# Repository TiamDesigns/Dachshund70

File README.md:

# Dachshund70

A tri-mode 60% keyboard I'm designing from scratch: the PCBs, the switch plate, the firmware, the config protocol, the driver and the configurator app. It runs over USB, Bluetooth LE and its own 2.4 GHz dongle, all on the nRF52840.

It was called the Dachshund60F until November 2026; older notes, PRs and the 26 October project review still use that name.

No boards have been made yet. All three PCBs are designed and the firmware is built and tested on a PC, so the next step is ordering them and bringing them up.

## Why I'm building this

I'm using this project to do two things at once:

1. **Explore hardware design with AI.** I want to see how far I can push an AI-assisted workflow on a real product: schematics, PCB layout, firmware, tooling and docs. I make the decisions and review everything, and Claude Code does a lot of the legwork. This repo is the record of how that went.
2. **Learn high-speed peripherals properly.** A keyboard looks simple, but doing it right covers USB device design, Bluetooth LE, a proprietary 2.4 GHz radio link, SPI and I2C displays, addressable LEDs, flash storage and power management. I want to understand each one well enough to design it, not just copy it.

And at the end of it I want a keyboard I actually enjoy using every day.

## Project goals

### Hardware

- Design all the boards myself in KiCad: the mainboard, a USB-C daughterboard and the dongle, plus an FR4 switch plate.
- Use a pre-certified nRF52840 module (Raytac MDBT50Q-P1MV2) and get the antenna keep-out, power and USB right the first time.
- Make it nice to type on: hot-swap switches, screw-in stabilisers, a gasket-mounted plate, and a horizontal roller encoder that turns like a mouse wheel.
- Run from USB or a single LiPo cell, with proper charging and a power path so it still works with the battery switched off.
- Measure everything when the boards arrive: rails, current draw in every state, scan rate, latency and radio range. The plan is in [docs/bringup-test-plan.md](docs/bringup-test-plan.md).

### Firmware

- Write my own firmware on Zephyr / nRF Connect SDK, not a fork of QMK or ZMK.
- Keep the keymap logic in plain C with no hardware in it, so it runs as unit tests on a PC.
- Be a complete USB keyboard: NKRO with boot-protocol fallback for BIOS and KVMs, media keys, lock LEDs, and suspend and remote wakeup.
- Support the advanced stuff: tap-hold, combos, tap dance, macros, key overrides, Caps Word, Auto Shift, Leader, mouse keys and the encoder.
- Never crash or corrupt flash on a bad packet. Every index and length from the host is checked, and the parser is fuzzed.

### Wireless

- Bluetooth LE HID with several host profiles and a switch key.
- A 2.4 GHz dongle on a second nRF52840 with low latency, polling at 1000 Hz (the limit for full-speed USB).
- Battery reporting, idle sleep and wake on key press.

### Driver and app

- No kernel driver. The board shows up as a normal HID keyboard plus one vendor-defined HID interface for configuration, so it works anywhere with nothing to install.
- A TypeScript host library (the "driver") that talks to that interface over WebHID in the browser or node-hid on the desktop.
- **Doghouse**, the configurator: keymap editing, advanced keys, macros, settings and firmware updates. It runs in Chrome or Edge, or as a desktop app for Windows, macOS and Linux that updates itself. It's in warm earth tones and dog-themed, because the boards are named after dogs.

### Doing it properly

- One protocol definition (`protocol/protocol.yaml`), with the C and TypeScript code generated from it.
- Versioned, CRC-checked, wear-levelled settings in flash, with migrations.
- CI that runs the unit tests, the host-library tests, the app build, protocol fuzzing, and debug and release firmware builds on every PR.
- Write down what changed and what's been tested in [PROGRESS.md](PROGRESS.md).

## The board

| | |
| --- | --- |
| MCU | nRF52840 (Raytac MDBT50Q-P1MV2 module) |
| Layout | 60% with an F-row, 80 switch positions, split or 6.25u spacebar |
| Matrix | 6 × 15, COL2ROW, diodes on every switch |
| Switches | Kailh hot-swap sockets (3 soldered positions on the spacebar row) |
| Encoder | Bourns PEC12R-2230F-S0024: shaft parallel to the board, 24 detents, push switch, 30 mm shaft, used as a 2u roller. On its own module board, cabled to the mainboard |
| Lighting | 6 × SK6812MINI-E indicators: layer, a 4-step battery gauge, and Caps Lock. No per-key RGB |
| Display | Optional OLED or e-paper on header J4 (panel not chosen yet) |
| Power | USB-C on a daughterboard, 1S LiPo on JST-PH, MCP73831 charger with a load-sharing power path |
| Connectivity | USB, Bluetooth LE, 2.4 GHz dongle |
| Bootloader | Adafruit nRF52 UF2 bootloader: double-tap reset and drag a `.uf2` onto the drive |
| USB IDs | pid.codes test PIDs 1209:0001 (keyboard), 1209:0002 (dongle), 1209:0003 (bootloader) |

## Where it's at

The firmware follows the build order in [SPEC.md](SPEC.md): wired first, then wireless.

| Phase | What it covers | Status |
| --- | --- | --- |
| 1 | Scaffold: monorepo, CI, Zephyr app | Done |
| 2 | Board bring-up, USB enumeration, UF2 bootloader | Done |
| 3 | Matrix scan, debounce, keycodes, layers, tap-hold | Done |
| 4 | Full USB HID: NKRO, media keys, lock LEDs, sleep and wake | Done |
| 5 | Config protocol v1 over a vendor HID interface | Done |
| 6 | Saving settings to flash | Done |
| 7 | Host library (WebHID and node-hid) | Done |
| 8 | Doghouse on real boards | Done |
| 9 | Advanced keys, macros and the encoder | Done |
| 10 | Indicator colours and global settings | Done |
| 11 | In-app firmware updates | Done |
| 12 | Bluetooth LE | Done |
| 13 | Power management, battery and input delay | Done |
| 14 | 2.4 GHz dongle firmware | Done |
| 15 | Desktop app packaging and auto-update | Done |

"Done" means built and tested on a PC and in CI. None of it has run on a real board yet, because there isn't one.

## Repo layout

| Folder | What's in it |
| --- | --- |
| `hardware/` | KiCad 10 projects: mainboard, USB-C daughterboard, dongle and plate, STEP exports, and the case (`hardware/case/`, CadQuery) |
| `boards/Dachshund70/` | Pin map, keyboard definition, Zephyr board files and the UF2 bootloader board |
| `boards/Pup/` | A one-key test board: the keyboard firmware on Nordic's nRF52840 Dongle, for trying the wireless outputs before the PCB exists |
| `firmware/` | The keyboard firmware. `firmware/core/` is the hardware-free keymap engine and its tests |
| `dongle/` | 2.4 GHz receiver firmware (see `dongle/README.md` to flash and pair it) |
| `protocol/` | `protocol.yaml` and the code generator |
| `host-lib/` | The TypeScript host library, mock board and tests |
| `app/` | Doghouse, the configurator (Svelte 5 + Vite), and its desktop app in `app/src-tauri/` (Tauri) |
| `docs/` | Bring-up and test plan, and my design decisions |

## Trying it out

You don't need a board to play with most of it.

**Doghouse with demo boards**

```sh
cd app
npm install
npm run dev
```

Then open http://localhost:5173/?demo. To use a real board, open http://localhost:5173 in Chrome or Edge and click **Connect a board…**.

**Tests**

```sh
# keymap engine and protocol (C, runs on the PC)
cmake -S firmware/core -B firmware/core/build
cmake --build firmware/core/build
ctest --test-dir firmware/core/build --output-on-failure

# host library
cd host-lib && npm ci && npm test
```

**Firmware**

From an nRF Connect SDK v3.4.1 shell, in the repo root:

```sh
west build -p -b dachshund70/nrf52840 -d build/firmware firmware -- -DBOARD_ROOT="$PWD"
```

[CLAUDE.md](CLAUDE.md) has every command, including release builds, display panels, the bootloader and flashing.

## Docs

- [SPEC.md](SPEC.md): scope and build order
- [PROGRESS.md](PROGRESS.md): what's done, what's tested, known issues
- [docs/design-decisions.md](docs/design-decisions.md): the decisions I made along the way and what I've learnt
- [docs/bringup-test-plan.md](docs/bringup-test-plan.md): how each board gets flashed, tested and measured
- [protocol/README.md](protocol/README.md): the config protocol
- [SCHEDULED_TASKS.md](SCHEDULED_TASKS.md): open tasks

## Licence and disclaimer

This is open source and open hardware. You're free to copy it, change it, build it and sell it.

- **Code** (firmware, host library, Doghouse, protocol, scripts) is under the [MIT License](LICENSE).
- **Hardware** (everything in `hardware/`: the three PCBs and the plate) is under the [CERN Open Hardware Licence v2, Permissive](hardware/LICENSE) (CERN-OHL-P-2.0).
- **Third-party files** keep their own licences. The keyswitch footprints and 3D models are CC-BY-SA-4.0 (see `hardware/Dachshund70/lib/README.md`), and the bootloader build fetches Adafruit's MIT-licensed source.

Both licences are permissive. You can make your own boards, fork the firmware, put it in a product, or sell keyboards based on it, commercially or not. All I ask, and all the licences require, is that you keep the copyright and licence notices with what you copy.

Please read this before you build one:

- **No warranty.** This is a personal learning project, provided as is. At the time of writing no board has been manufactured or tested, so the designs may have mistakes. Check them yourself before ordering.
- **Lithium batteries can be dangerous.** The board charges a LiPo cell. Use a cell with its own protection circuit, check the connector polarity (JST-PH polarity isn't standard between vendors), and don't leave it charging unattended until you've tested your build.
- **USB IDs: change them before you give a board to anyone.** I've chosen not to register USB IDs for this project, because my board only lives on my desk. The firmware uses pid.codes *test* PIDs (1209:0001, 0002 and 0003), which anyone may use for in-house testing but which **must not** be used on a device that's given away, sold or manufactured. Every board using them looks identical to the OS, and to every other project that uses the same test IDs. If your boards will leave your hands, get your own VID/PID (a free PID from [pid.codes](https://pid.codes/howto/) for open-source hardware, or a VID from the USB-IF) and change them in `firmware/Kconfig`, the dongle and bootloader configs, and `boards/Dachshund70/board.json`.
- **Certification.** The radio module is pre-certified, but a finished product may still need its own testing (FCC, CE and so on) before you sell it. That's on you.

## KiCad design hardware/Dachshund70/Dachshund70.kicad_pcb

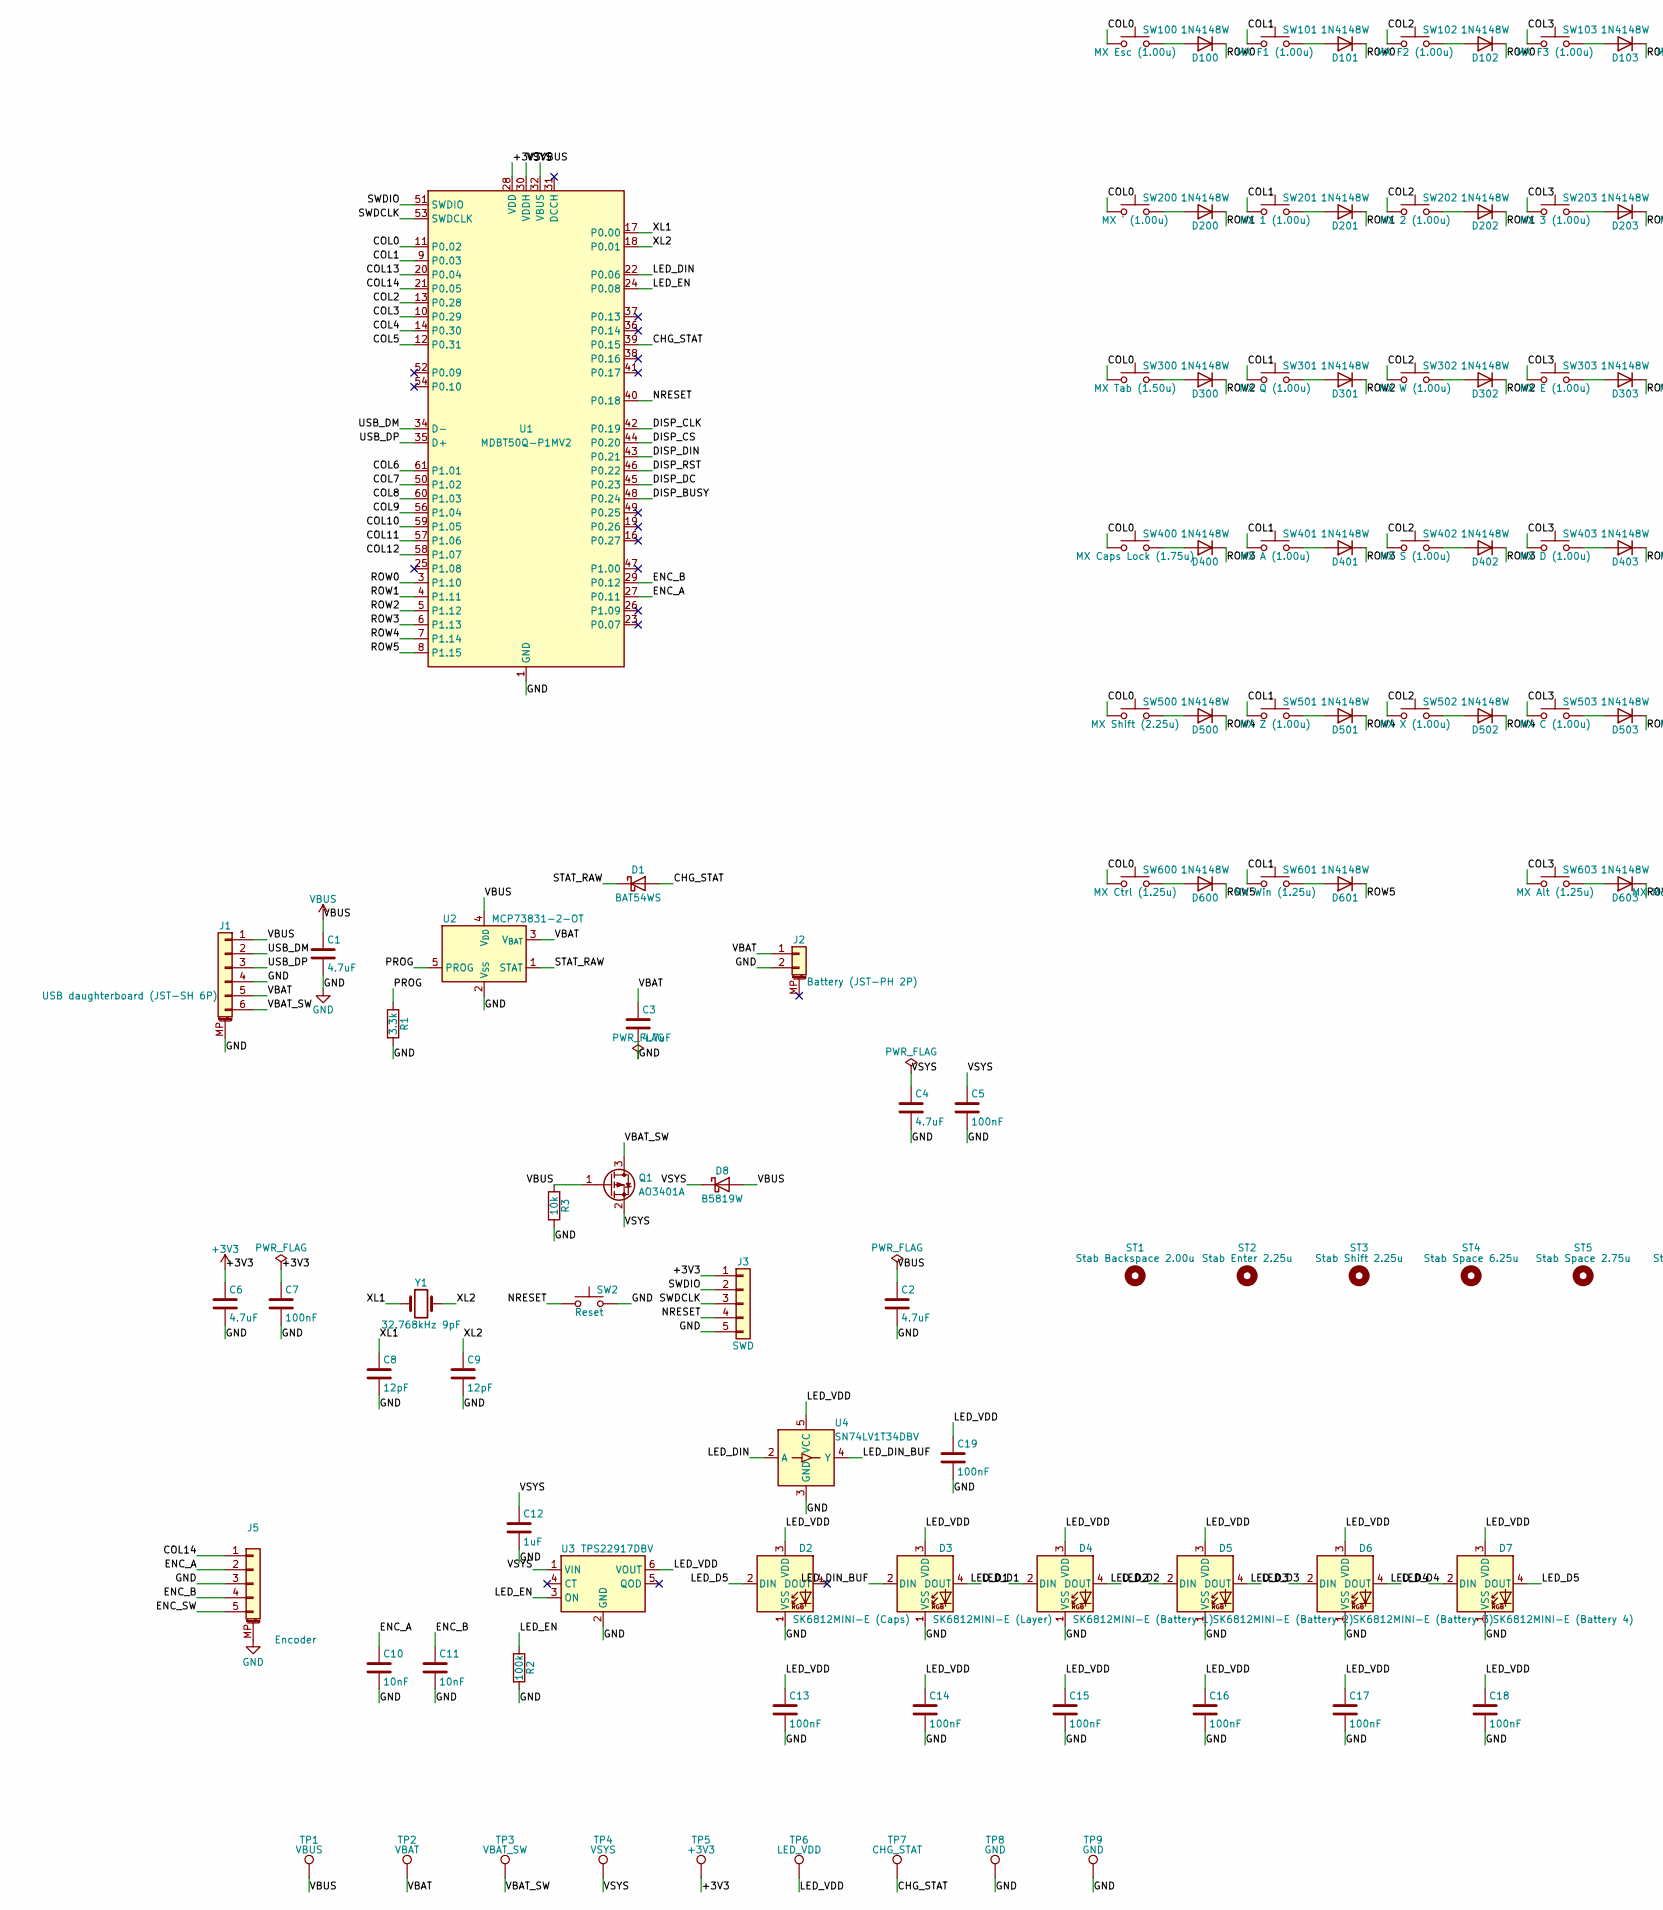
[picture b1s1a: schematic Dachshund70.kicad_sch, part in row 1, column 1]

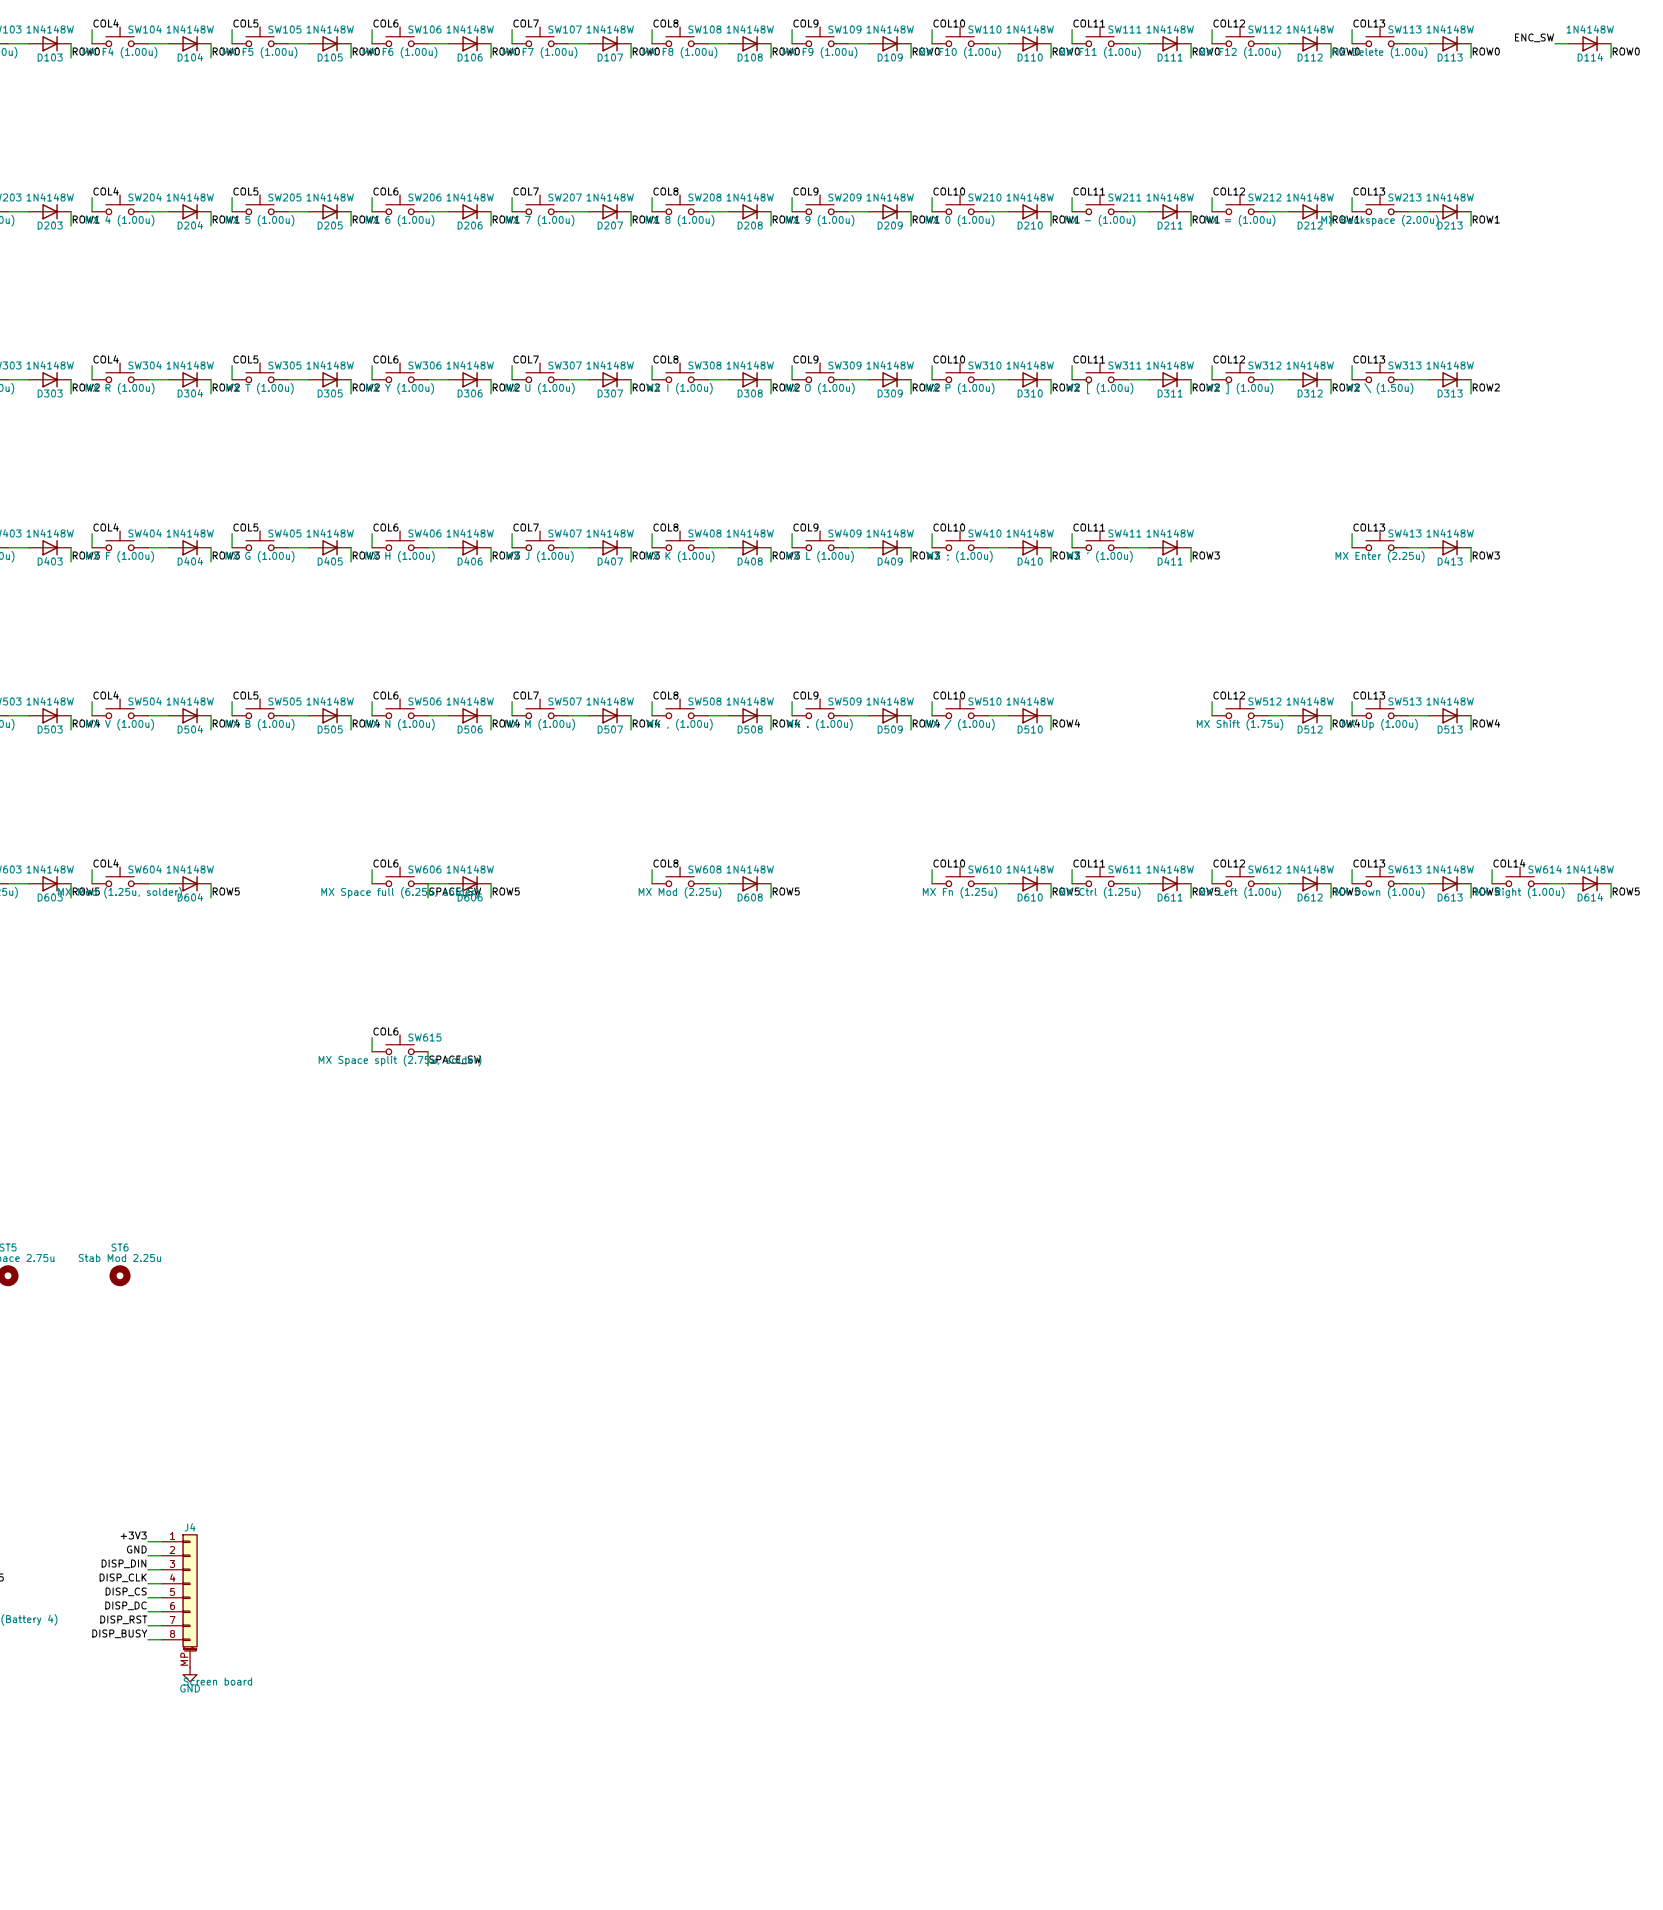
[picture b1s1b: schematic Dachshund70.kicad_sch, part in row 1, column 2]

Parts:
C1, C2, C3, C4, C6: 4.7uF; C_0603_1608Metric; MPN Samsung CL10A475KO8NNNC; LCSC C19666
C5, C7, C13, C14, C15, C16, C17, C18, C19: 100nF; C_0402_1005Metric; MPN Samsung CL05B104KO5NNNC; LCSC C1525
C8, C9: 12pF; C_0402_1005Metric; MPN FH 0402CG120J500NT; LCSC C1547
C10, C11: 10nF; C_0402_1005Metric; MPN Samsung CL05B103KB5NNNC; LCSC C15195
C12: 1uF; C_0402_1005Metric; MPN Samsung CL05A105KA5NQNC; LCSC C52923
D1: BAT54WS; D_SOD-323; MPN CJ BAT54WS; LCSC C2991936
D2: SK6812MINI-E (Caps); LED_SK6812MINI-E_3.2x2.8mm_P1.5mm_ReverseMount_Cutout3.4; MPN OPSCO SK6812MINI-E; LCSC C5149201
D3: SK6812MINI-E (Layer); LED_SK6812MINI-E_3.2x2.8mm_P1.5mm_ReverseMount_Cutout3.4; MPN OPSCO SK6812MINI-E; LCSC C5149201
D4: SK6812MINI-E (Battery 1); LED_SK6812MINI-E_3.2x2.8mm_P1.5mm_ReverseMount_Cutout3.4; MPN OPSCO SK6812MINI-E; LCSC C5149201
D5: SK6812MINI-E (Battery 2); LED_SK6812MINI-E_3.2x2.8mm_P1.5mm_ReverseMount_Cutout3.4; MPN OPSCO SK6812MINI-E; LCSC C5149201
D6: SK6812MINI-E (Battery 3); LED_SK6812MINI-E_3.2x2.8mm_P1.5mm_ReverseMount_Cutout3.4; MPN OPSCO SK6812MINI-E; LCSC C5149201
D7: SK6812MINI-E (Battery 4); LED_SK6812MINI-E_3.2x2.8mm_P1.5mm_ReverseMount_Cutout3.4; MPN OPSCO SK6812MINI-E; LCSC C5149201
D8: B5819W; D_SOD-123; MPN B5819W SL; LCSC C8598
D100, D101, D102, D103, D104, D105, D106, D107, D108, D109, D110, D111, D112, D113, D114, D200, D201, D202, D203, D204, D205, D206, D207, D208, D209, D210, D211, D212, D213, D300, D301, D302, D303, D304, D305, D306, D307, D308, D309, D310, D311, D312, D313, D400, D401, D402, D403, D404, D405, D406, D407, D408, D409, D410, D411, D413, D500, D501, D502, D503, D504, D505, D506, D507, D508, D509, D510, D512, D513, D600, D601, D603, D604, D606, D608, D610, D611, D612, D613, D614: 1N4148W; D_SOD-123; MPN 1N4148W; LCSC C81598
J1: USB daughterboard (JST-SH 6P); JST_SH_SM06B-SRSS-TB_1x06-1MP_P1.00mm_Horizontal; MPN JST SM06B-SRSS-TB(LF)(SN); LCSC C160405
J2: Battery (JST-PH 2P); JST_PH_S2B-PH-SM4-TB_1x02-1MP_P2.00mm_Horizontal; MPN JST S2B-PH-SM4-TB(LF)(SN); LCSC C295747
J3: SWD; PinHeader_1x05_P1.27mm_Vertical; MPN XFCN PZ127V-11-05-H25; LCSC C962329
J4: Screen board; Hirose_FH12-8S-0.5SH_1x08-1MP_P0.50mm_Horizontal; MPN Hirose FH12-8S-0.5SH(55)
J5: Encoder; JST_SH_SM05B-SRSS-TB_1x05-1MP_P1.00mm_Horizontal; MPN JST SM05B-SRSS-TB
Q1: AO3401A; SOT-23; MPN AO3401A; LCSC C15127
R1: 3.3k; R_0603_1608Metric; MPN UNI-ROYAL 0603WAF3301T5E; LCSC C22978
R2: 100k; R_0402_1005Metric; MPN UNI-ROYAL 0402WGF1003TCE; LCSC C25741
R3: 10k; R_0603_1608Metric; MPN UNI-ROYAL 0603WAF1002T5E; LCSC C25804
ST1: Stab Backspace 2.00u; Stabilizer_Cherry_MX_2.00u
ST2: Stab Enter 2.25u; Stabilizer_Cherry_MX_2.00u
ST3: Stab Shift 2.25u; Stabilizer_Cherry_MX_2.00u
ST4: Stab Space 6.25u; Stabilizer_Cherry_MX_6.25u
ST5: Stab Space 2.75u; Stabilizer_Cherry_MX_2.00u
ST6: Stab Mod 2.25u; Stabilizer_Cherry_MX_2.00u
SW2: Reset; SW_SPST_TL3342; MPN E-Switch TL3342F160QG; LCSC C2886898
SW100: MX Esc (1.00u); SW_Hotswap_Kailh_MX_1.00u; MPN HanElectricity CPG151101S11-2 (Kailh-pa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; LCSC C49352235
SW101: MX F1 (1.00u); SW_Hotswap_Kailh_MX_1.00u; MPN HanElectricity CPG151101S11-2 (Kailh-pa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; LCSC C49352235
SW102: MX F2 (1.00u); SW_Hotswap_Kailh_MX_1.00u; MPN HanElectricity CPG151101S11-2 (Kailh-pa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; LCSC C49352235
SW103: MX F3 (1.00u); SW_Hotswap_Kailh_MX_1.00u; MPN HanElectricity CPG151101S11-2 (Kailh-pa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; LCSC C49352235
SW104: MX F4 (1.00u); SW_Hotswap_Kailh_MX_1.00u; MPN HanElectricity CPG151101S11-2 (Kailh-pa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; LCSC C49352235
SW105: MX F5 (1.00u); SW_Hotswap_Kailh_MX_1.00u; MPN HanElectricity CPG151101S11-2 (Kailh-pa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; LCSC C49352235
SW106: MX F6 (1.00u); SW_Hotswap_Kailh_MX_1.00u; MPN HanElectricity CPG151101S11-2 (Kailh-pa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; LCSC C49352235
SW107: MX F7 (1.00u); SW_Hotswap_Kailh_MX_1.00u; MPN HanElectricity CPG151101S11-2 (Kailh-pa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; LCSC C49352235
SW108: MX F8 (1.00u); SW_Hotswap_Kailh_MX_1.00u; MPN HanElectricity CPG151101S11-2 (Kailh-pa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; LCSC C49352235
SW109: MX F9 (1.00u); SW_Hotswap_Kailh_MX_1.00u; MPN HanElectricity CPG151101S11-2 (Kailh-pa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; LCSC C49352235
SW110: MX F10 (1.00u); SW_Hotswap_Kailh_MX_1.00u; MPN HanElectricity CPG151101S11-2 (Kailh-pa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; LCSC C49352235
SW111: MX F11 (1.00u); SW_Hotswap_Kailh_MX_1.00u; MPN HanElectricity CPG151101S11-2 (Kailh-pa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; LCSC C49352235
SW112: MX F12 (1.00u); SW_Hotswap_Kailh_MX_1.00u; MPN HanElectricity CPG151101S11-2 (Kailh-pa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; LCSC C49352235
SW113: MX Delete (1.00u); SW_Hotswap_Kailh_MX_1.00u; MPN HanElectricity CPG151101S11-2 (Kailh-pa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; LCSC C49352235
SW200: MX ` (1.00u); SW_Hotswap_Kailh_MX_1.00u; MPN HanElectricity CPG151101S11-2 (Kailh-pa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; LCSC C49352235
SW201: MX 1 (1.00u); SW_Hotswap_Kailh_MX_1.00u; MPN HanElectricity CPG151101S11-2 (Kailh-pa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; LCSC C49352235
SW202: MX 2 (1.00u); SW_Hotswap_Kailh_MX_1.00u; MPN HanElectricity CPG151101S11-2 (Kailh-pa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; LCSC C49352235
SW203: MX 3 (1.00u); SW_Hotswap_Kailh_MX_1.00u; MPN HanElectricity CPG151101S11-2 (Kailh-pa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; LCSC C49352235
SW204: MX 4 (1.00u); SW_Hotswap_Kailh_MX_1.00u; MPN HanElectricity CPG151101S11-2 (Kailh-pa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; LCSC C49352235
SW205: MX 5 (1.00u); SW_Hotswap_Kailh_MX_1.00u; MPN HanElectricity CPG151101S11-2 (Kailh-pa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; LCSC C49352235
SW206: MX 6 (1.00u); SW_Hotswap_Kailh_MX_1.00u; MPN HanElectricity CPG151101S11-2 (Kailh-pa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; LCSC C49352235
SW207: MX 7 (1.00u); SW_Hotswap_Kailh_MX_1.00u; MPN HanElectricity CPG151101S11-2 (Kailh-pa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; LCSC C49352235
SW208: MX 8 (1.00u); SW_Hotswap_Kailh_MX_1.00u; MPN HanElectricity CPG151101S11-2 (Kailh-pa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; LCSC C49352235
SW209: MX 9 (1.00u); SW_Hotswap_Kailh_MX_1.00u; MPN HanElectricity CPG151101S11-2 (Kailh-pa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; LCSC C49352235
SW210: MX 0 (1.00u); SW_Hotswap_Kailh_MX_1.00u; MPN HanElectricity CPG151101S11-2 (Kailh-pa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; LCSC C49352235
SW211: MX - (1.00u); SW_Hotswap_Kailh_MX_1.00u; MPN HanElectricity CPG151101S11-2 (Kailh-pa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; LCSC C49352235
SW212: MX = (1.00u); SW_Hotswap_Kailh_MX_1.00u; MPN HanElectricity CPG151101S11-2 (Kailh-pa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; LCSC C49352235
SW213: MX Backspace (2.00u); SW_Hotswap_Kailh_MX_2.00u; MPN HanElectricity CPG151101S11-2 (Kailh-pa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; LCSC C49352235
SW300: MX Tab (1.50u); SW_Hotswap_Kailh_MX_1.50u; MPN HanElectricity CPG151101S11-2 (Kailh-pa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; LCSC C49352235
SW301: MX Q (1.00u); SW_Hotswap_Kailh_MX_1.00u; MPN HanElectricity CPG151101S11-2 (Kailh-pa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; LCSC C49352235
SW302: MX W (1.00u); SW_Hotswap_Kailh_MX_1.00u; MPN HanElectricity CPG151101S11-2 (Kailh-pa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; LCSC C49352235
SW303: MX E (1.00u); SW_Hotswap_Kailh_MX_1.00u; MPN HanElectricity CPG151101S11-2 (Kailh-pa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; LCSC C49352235
SW304: MX R (1.00u); SW_Hotswap_Kailh_MX_1.00u; MPN HanElectricity CPG151101S11-2 (Kailh-pa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; LCSC C49352235
SW305: MX T (1.00u); SW_Hotswap_Kailh_MX_1.00u; MPN HanElectricity CPG151101S11-2 (Kailh-pa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; LCSC C49352235
SW306: MX Y (1.00u); SW_Hotswap_Kailh_MX_1.00u; MPN HanElectricity CPG151101S11-2 (Kailh-pa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; LCSC C49352235
SW307: MX U (1.00u); SW_Hotswap_Kailh_MX_1.00u; MPN HanElectricity CPG151101S11-2 (Kailh-pa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; LCSC C49352235
SW308: MX I (1.00u); SW_Hotswap_Kailh_MX_1.00u; MPN HanElectricity CPG151101S11-2 (Kailh-pa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; LCSC C49352235
SW309: MX O (1.00u); SW_Hotswap_Kailh_MX_1.00u; MPN HanElectricity CPG151101S11-2 (Kailh-pa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; LCSC C49352235
SW310: MX P (1.00u); SW_Hotswap_Kailh_MX_1.00u; MPN HanElectricity CPG151101S11-2 (Kailh-pa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; LCSC C49352235
SW311: MX [ (1.00u); SW_Hotswap_Kailh_MX_1.00u; MPN HanElectricity CPG151101S11-2 (Kailh-pa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; LCSC C49352235
SW312: MX ] (1.00u); SW_Hotswap_Kailh_MX_1.00u; MPN HanElectricity CPG151101S11-2 (Kailh-pa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; LCSC C49352235
SW313: MX \ (1.50u); SW_Hotswap_Kailh_MX_1.50u; MPN HanElectricity CPG151101S11-2 (Kailh-pa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; LCSC C49352235
SW400: MX Caps Lock (1.75u); SW_Hotswap_Kailh_MX_1.75u; MPN HanElectricity CPG151101S11-2 (Kailh-pa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; LCSC C49352235
SW401: MX A (1.00u); SW_Hotswap_Kailh_MX_1.00u; MPN HanElectricity CPG151101S11-2 (Kailh-pa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; LCSC C49352235
SW402: MX S (1.00u); SW_Hotswap_Kailh_MX_1.00u; MPN HanElectricity CPG151101S11-2 (Kailh-pa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; LCSC C49352235
SW403: MX D (1.00u); SW_Hotswap_Kailh_MX_1.00u; MPN HanElectricity CPG151101S11-2 (Kailh-pa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; LCSC C49352235
SW404: MX F (1.00u); SW_Hotswap_Kailh_MX_1.00u; MPN HanElectricity CPG151101S11-2 (Kailh-pa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; LCSC C49352235
SW405: MX G (1.00u); SW_Hotswap_Kailh_MX_1.00u; MPN HanElectricity CPG151101S11-2 (Kailh-pa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; LCSC C49352235
SW406: MX H (1.00u); SW_Hotswap_Kailh_MX_1.00u; MPN HanElectricity CPG151101S11-2 (Kailh-pa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; LCSC C49352235
SW407: MX J (1.00u); SW_Hotswap_Kailh_MX_1.00u; MPN HanElectricity CPG151101S11-2 (Kailh-pa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; LCSC C49352235
SW408: MX K (1.00u); SW_Hotswap_Kailh_MX_1.00u; MPN HanElectricity CPG151101S11-2 (Kailh-pa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; LCSC C49352235
SW409: MX L (1.00u); SW_Hotswap_Kailh_MX_1.00u; MPN HanElectricity CPG151101S11-2 (Kailh-pa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; LCSC C49352235
SW410: MX ; (1.00u); SW_Hotswap_Kailh_MX_1.00u; MPN HanElectricity CPG151101S11-2 (Kailh-pa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; LCSC C49352235
SW411: MX ' (1.00u); SW_Hotswap_Kailh_MX_1.00u; MPN HanElectricity CPG151101S11-2 (Kailh-pa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; LCSC C49352235
SW413: MX Enter (2.25u); SW_Hotswap_Kailh_MX_2.25u; MPN HanElectricity CPG151101S11-2 (Kailh-pa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; LCSC C49352235
SW500: MX Shift (2.25u); SW_Hotswap_Kailh_MX_2.25u; MPN HanElectricity CPG151101S11-2 (Kailh-pa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; LCSC C49352235
SW501: MX Z (1.00u); SW_Hotswap_Kailh_MX_1.00u; MPN HanElectricity CPG151101S11-2 (Kailh-pa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; LCSC C49352235
SW502: MX X (1.00u); SW_Hotswap_Kailh_MX_1.00u; MPN HanElectricity CPG151101S11-2 (Kailh-pa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; LCSC C49352235
SW503: MX C (1.00u); SW_Hotswap_Kailh_MX_1.00u; MPN HanElectricity CPG151101S11-2 (Kailh-pa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; LCSC C49352235
SW504: MX V (1.00u); SW_Hotswap_Kailh_MX_1.00u; MPN HanElectricity CPG151101S11-2 (Kailh-pa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; LCSC C49352235
SW505: MX B (1.00u); SW_Hotswap_Kailh_MX_1.00u; MPN HanElectricity CPG151101S11-2 (Kailh-pa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; LCSC C49352235
SW506: MX N (1.00u); SW_Hotswap_Kailh_MX_1.00u; MPN HanElectricity CPG151101S11-2 (Kailh-pa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; LCSC C49352235
SW507: MX M (1.00u); SW_Hotswap_Kailh_MX_1.00u; MPN HanElectricity CPG151101S11-2 (Kailh-pa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; LCSC C49352235
SW508: MX , (1.00u); SW_Hotswap_Kailh_MX_1.00u; MPN HanElectricity CPG151101S11-2 (Kailh-pa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; LCSC C49352235
SW509: MX . (1.00u); SW_Hotswap_Kailh_MX_1.00u; MPN HanElectricity CPG151101S11-2 (Kailh-pa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; LCSC C49352235
SW510: MX / (1.00u); SW_Hotswap_Kailh_MX_1.00u; MPN HanElectricity CPG151101S11-2 (Kailh-pa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; LCSC C49352235
SW512: MX Shift (1.75u); SW_Hotswap_Kailh_MX_1.75u; MPN HanElectricity CPG151101S11-2 (Kailh-pa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; LCSC C49352235
SW513: MX Up (1.00u); SW_Hotswap_Kailh_MX_1.00u; MPN HanElectricity CPG151101S11-2 (Kailh-pa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; LCSC C49352235
SW600, SW611: MX Ctrl (1.25u); SW_Hotswap_Kailh_MX_1.25u; MPN HanElectricity CPG151101S11-2 (Kailh-pa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; LCSC C49352235
SW601: MX Win (1.25u); SW_Hotswap_Kailh_MX_1.25u; MPN HanElectricity CPG151101S11-2 (Kailh-pa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; LCSC C49352235
SW603: MX Alt (1.25u); SW_Hotswap_Kailh_MX_1.25u; MPN HanElectricity CPG151101S11-2 (Kailh-pa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; LCSC C49352235
SW604: MX Mod (1.25u, solder); SW_Cherry_MX_1.25u_Plate
SW606: MX Space full (6.25u, solder); SW_Cherry_MX_6.25u_Plate
SW608: MX Mod (2.25u); SW_Hotswap_Kailh_MX_2.25u; MPN HanElectricity CPG151101S11-2 (Kailh-pa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; LCSC C49352235
SW610: MX Fn (1.25u); SW_Hotswap_Kailh_MX_1.25u; MPN HanElectricity CPG151101S11-2 (Kailh-pa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; LCSC C49352235
SW612: MX Left (1.00u); SW_Hotswap_Kailh_MX_1.00u; MPN HanElectricity CPG151101S11-2 (Kailh-pa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; LCSC C49352235
SW613: MX Down (1.00u); SW_Hotswap_Kailh_MX_1.00u; MPN HanElectricity CPG151101S11-2 (Kailh-pa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; LCSC C49352235
SW614: MX Right (1.00u); SW_Hotswap_Kailh_MX_1.00u; MPN HanElectricity CPG151101S11-2 (Kailh-pa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; LCSC C49352235
SW615: MX Space split (2.75u, solder); SW_Cherry_MX_2.75u_Plate
TP1: VBUS; TestPoint_Pad_D1.5mm
TP2: VBAT; TestPoint_Pad_D1.5mm
TP3: VBAT_SW; TestPoint_Pad_D1.5mm
TP4: VSYS; TestPoint_Pad_D1.5mm
TP5: +3V3; TestPoint_Pad_D1.5mm
TP6: LED_VDD; TestPoint_Pad_D1.5mm
TP7: CHG_STAT; TestPoint_Pad_D1.5mm
TP8, TP9: GND; TestPoint_Pad_D1.5mm
U1: MDBT50Q-P1MV2; Raytac_MDBT50Q; MPN Raytac MDBT50Q-P1MV2; LCSC C5119772
U2: MCP73831-2-OT; SOT-23-5; MPN Microchip MCP73831T-2ACI/OT; LCSC C424093
U3: TPS22917DBV; SOT-23-6; MPN TI TPS22917DBVR; LCSC C2681320
U4: SN74LV1T34DBV; SOT-23-5; MPN TI SN74LV1T34DBVR; LCSC C100024
Y1: 32.768kHz 9pF; Crystal_SMD_3215-2Pin_3.2x1.5mm; MPN Epson X1A0000910005 (32.768 kHz, 9 pF); LCSC C255869

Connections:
+3V3: C6.1, C7.1, J3.1, J4.1, TP5.1, U1.28 (VDD)
/CHG_STAT: D1.2 (A), TP7.1, U1.39 (P0.15)
/COL0: SW100.1, SW200.1, SW300.1, SW400.1, SW500.1, SW600.1, U1.11 (P0.02)
/COL1: SW101.1, SW201.1, SW301.1, SW401.1, SW501.1, SW601.1, U1.9 (P0.03)
/COL2: SW102.1, SW202.1, SW302.1, SW402.1, SW502.1, U1.13 (P0.28)
/COL3: SW103.1, SW203.1, SW303.1, SW403.1, SW503.1, SW603.1, U1.10 (P0.29)
/COL4: SW104.1, SW204.1, SW304.1, SW404.1, SW504.1, SW604.1, U1.14 (P0.30)
/COL5: SW105.1, SW205.1, SW305.1, SW405.1, SW505.1, U1.12 (P0.31)
/COL6: SW106.1, SW206.1, SW306.1, SW406.1, SW506.1, SW606.1, SW615.1, U1.61 (P1.01)
/COL7: SW107.1, SW207.1, SW307.1, SW407.1, SW507.1, U1.50 (P1.02)
/COL8: SW108.1, SW208.1, SW308.1, SW408.1, SW508.1, SW608.1, U1.60 (P1.03)
/COL9: SW109.1, SW209.1, SW309.1, SW409.1, SW509.1, U1.56 (P1.04)
/COL10: SW110.1, SW210.1, SW310.1, SW410.1, SW510.1, SW610.1, U1.59 (P1.05)
/COL11: SW111.1, SW211.1, SW311.1, SW411.1, SW611.1, U1.57 (P1.06)
/COL12: SW112.1, SW212.1, SW312.1, SW512.1, SW612.1, U1.58 (P1.07)
/COL13: SW113.1, SW213.1, SW313.1, SW413.1, SW513.1, SW613.1, U1.20 (P0.04)
/COL14: J5.1, SW614.1, U1.21 (P0.05)
/DISP_BUSY: J4.8, U1.48 (P0.24)
/DISP_CLK: J4.4, U1.42 (P0.19)
/DISP_CS: J4.5, U1.44 (P0.20)
/DISP_DC: J4.6, U1.45 (P0.23)
/DISP_DIN: J4.3, U1.43 (P0.21)
/DISP_RST: J4.7, U1.46 (P0.22)
/ENC_A: C10.1, J5.2, U1.27 (P0.11)
/ENC_B: C11.1, J5.4, U1.29 (P0.12)
/ENC_SW: D114.2 (A), J5.5
/LED_D1: D3.4 (DOUT), D4.2 (DIN)
/LED_D2: D4.4 (DOUT), D5.2 (DIN)
/LED_D3: D5.4 (DOUT), D6.2 (DIN)
/LED_D4: D6.4 (DOUT), D7.2 (DIN)
/LED_D5: D2.2 (DIN), D7.4 (DOUT)
/LED_DIN: U1.22 (P0.06), U4.2 (A)
/LED_DIN_BUF: D3.2 (DIN), U4.4 (Y)
/LED_EN: R2.1, U1.24 (P0.08), U3.3 (ON)
/LED_VDD: C13.1, C14.1, C15.1, C16.1, C17.1, C18.1, C19.1, D2.3 (VDD), D3.3 (VDD), D4.3 (VDD), D5.3 (VDD), D6.3 (VDD), D7.3 (VDD), TP6.1, U3.6 (VOUT), U4.5 (VCC)
/NRESET: J3.4, SW2.1, U1.40 (P0.18)
/PROG: R1.1, U2.5 (PROG)
/ROW0: D100.1 (K), D101.1 (K), D102.1 (K), D103.1 (K), D104.1 (K), D105.1 (K), D106.1 (K), D107.1 (K), D108.1 (K), D109.1 (K), D110.1 (K), D111.1 (K), D112.1 (K), D113.1 (K), D114.1 (K), U1.3 (P1.10)
/ROW1: D200.1 (K), D201.1 (K), D202.1 (K), D203.1 (K), D204.1 (K), D205.1 (K), D206.1 (K), D207.1 (K), D208.1 (K), D209.1 (K), D210.1 (K), D211.1 (K), D212.1 (K), D213.1 (K), U1.4 (P1.11)
/ROW2: D300.1 (K), D301.1 (K), D302.1 (K), D303.1 (K), D304.1 (K), D305.1 (K), D306.1 (K), D307.1 (K), D308.1 (K), D309.1 (K), D310.1 (K), D311.1 (K), D312.1 (K), D313.1 (K), U1.5 (P1.12)
/ROW3: D400.1 (K), D401.1 (K), D402.1 (K), D403.1 (K), D404.1 (K), D405.1 (K), D406.1 (K), D407.1 (K), D408.1 (K), D409.1 (K), D410.1 (K), D411.1 (K), D413.1 (K), U1.6 (P1.13)
/ROW4: D500.1 (K), D501.1 (K), D502.1 (K), D503.1 (K), D504.1 (K), D505.1 (K), D506.1 (K), D507.1 (K), D508.1 (K), D509.1 (K), D510.1 (K), D512.1 (K), D513.1 (K), U1.7 (P1.14)
/ROW5: D600.1 (K), D601.1 (K), D603.1 (K), D604.1 (K), D606.1 (K), D608.1 (K), D610.1 (K), D611.1 (K), D612.1 (K), D613.1 (K), D614.1 (K), U1.8 (P1.15)
/SPACE_SW: D606.2 (A), SW606.2, SW615.2
/STAT_RAW: D1.1 (K), U2.1 (STAT)
/SWDCLK: J3.3, U1.53 (SWDCLK)
/SWDIO: J3.2, U1.51 (SWDIO)
/USB_DM: J1.2, U1.34 (D-)
/USB_DP: J1.3, U1.35 (D+)
/VBAT: C3.1, J1.5, J2.1, TP2.1, U2.3 (V_{BAT})
/VBAT_SW: J1.6, Q1.3 (D), TP3.1
/VSYS: C4.1, C5.1, C12.1, D8.1 (K), Q1.2 (S), TP4.1, U1.30 (VDDH), U3.1 (VIN)
/XL1: C8.1, U1.17 (P0.00), Y1.1
/XL2: C9.1, U1.18 (P0.01), Y1.2
GND: C1.2, C2.2, C3.2, C4.2, C5.2, C6.2, C7.2, C8.2, C9.2, C10.2, C11.2, C12.2, C13.2, C14.2, C15.2, C16.2, C17.2, C18.2, C19.2, D2.1 (VSS), D3.1 (VSS), D4.1 (VSS), D5.1 (VSS), D6.1 (VSS), D7.1 (VSS), J1.4, J1.MP (MountPin), J2.2, J3.5, J4.2, J4.MP (MountPin), J5.3, J5.MP (MountPin), R1.2, R2.2, R3.2, SW2.2, TP8.1, TP9.1, U1.1 (GND), U1.2 (GND), U1.15 (GND), U1.33 (GND), U1.55 (GND), U2.2 (V_{SS}), U3.2 (GND), U4.3 (GND)
unnamed: D100.2 (A), SW100.2
unnamed: D101.2 (A), SW101.2
unnamed: D102.2 (A), SW102.2
unnamed: D103.2 (A), SW103.2
unnamed: D104.2 (A), SW104.2
unnamed: D105.2 (A), SW105.2
unnamed: D106.2 (A), SW106.2
unnamed: D107.2 (A), SW107.2
unnamed: D108.2 (A), SW108.2
unnamed: D109.2 (A), SW109.2
unnamed: D110.2 (A), SW110.2
unnamed: D111.2 (A), SW111.2
unnamed: D112.2 (A), SW112.2
unnamed: D113.2 (A), SW113.2
unnamed: D200.2 (A), SW200.2
unnamed: D201.2 (A), SW201.2
unnamed: D202.2 (A), SW202.2
unnamed: D203.2 (A), SW203.2
unnamed: D204.2 (A), SW204.2
unnamed: D205.2 (A), SW205.2
unnamed: D206.2 (A), SW206.2
unnamed: D207.2 (A), SW207.2
unnamed: D208.2 (A), SW208.2
unnamed: D209.2 (A), SW209.2
unnamed: D210.2 (A), SW210.2
unnamed: D211.2 (A), SW211.2
unnamed: D212.2 (A), SW212.2
unnamed: D213.2 (A), SW213.2
unnamed: D300.2 (A), SW300.2
unnamed: D301.2 (A), SW301.2
unnamed: D302.2 (A), SW302.2
unnamed: D303.2 (A), SW303.2
unnamed: D304.2 (A), SW304.2
unnamed: D305.2 (A), SW305.2
unnamed: D306.2 (A), SW306.2
unnamed: D307.2 (A), SW307.2
unnamed: D308.2 (A), SW308.2
unnamed: D309.2 (A), SW309.2
unnamed: D310.2 (A), SW310.2
unnamed: D311.2 (A), SW311.2
unnamed: D312.2 (A), SW312.2
unnamed: D313.2 (A), SW313.2
unnamed: D400.2 (A), SW400.2
unnamed: D401.2 (A), SW401.2
unnamed: D402.2 (A), SW402.2
unnamed: D403.2 (A), SW403.2
unnamed: D404.2 (A), SW404.2
unnamed: D405.2 (A), SW405.2
unnamed: D406.2 (A), SW406.2
unnamed: D407.2 (A), SW407.2
unnamed: D408.2 (A), SW408.2
unnamed: D409.2 (A), SW409.2
unnamed: D410.2 (A), SW410.2
unnamed: D411.2 (A), SW411.2
unnamed: D413.2 (A), SW413.2
unnamed: D500.2 (A), SW500.2
unnamed: D501.2 (A), SW501.2
unnamed: D502.2 (A), SW502.2
unnamed: D503.2 (A), SW503.2
unnamed: D504.2 (A), SW504.2
unnamed: D505.2 (A), SW505.2
unnamed: D506.2 (A), SW506.2
unnamed: D507.2 (A), SW507.2
unnamed: D508.2 (A), SW508.2
unnamed: D509.2 (A), SW509.2
unnamed: D510.2 (A), SW510.2
unnamed: D512.2 (A), SW512.2
unnamed: D513.2 (A), SW513.2
unnamed: D600.2 (A), SW600.2
unnamed: D601.2 (A), SW601.2
unnamed: D603.2 (A), SW603.2
unnamed: D604.2 (A), SW604.2
unnamed: D608.2 (A), SW608.2
unnamed: D610.2 (A), SW610.2
unnamed: D611.2 (A), SW611.2
unnamed: D612.2 (A), SW612.2
unnamed: D613.2 (A), SW613.2
unnamed: D614.2 (A), SW614.2
VBUS: C1.1, C2.1, D8.2 (A), J1.1, Q1.1 (G), R3.1, TP1.1, U1.32 (VBUS), U2.4 (V_{DD})

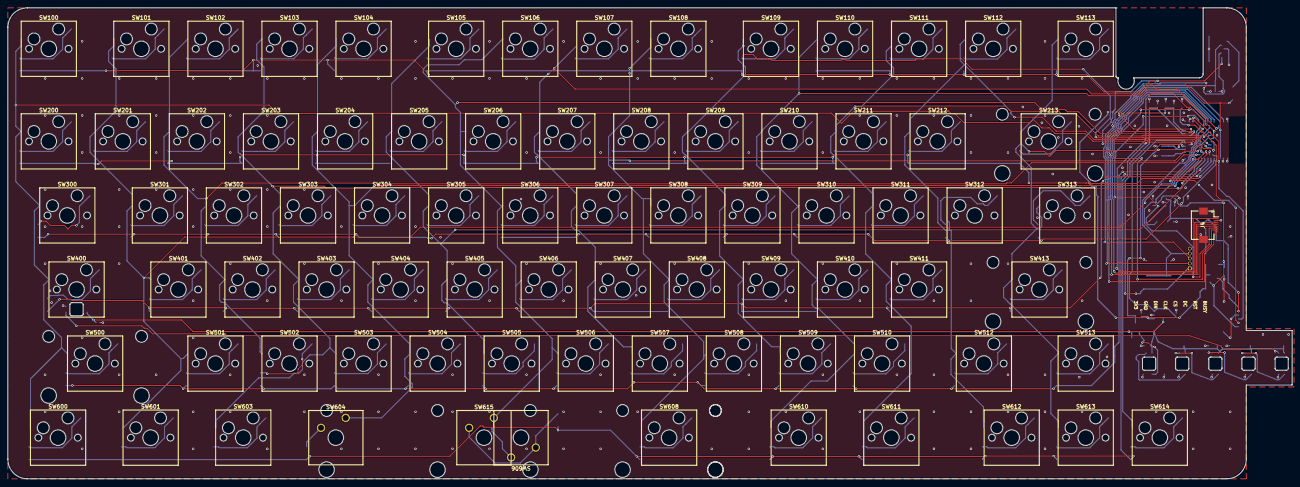
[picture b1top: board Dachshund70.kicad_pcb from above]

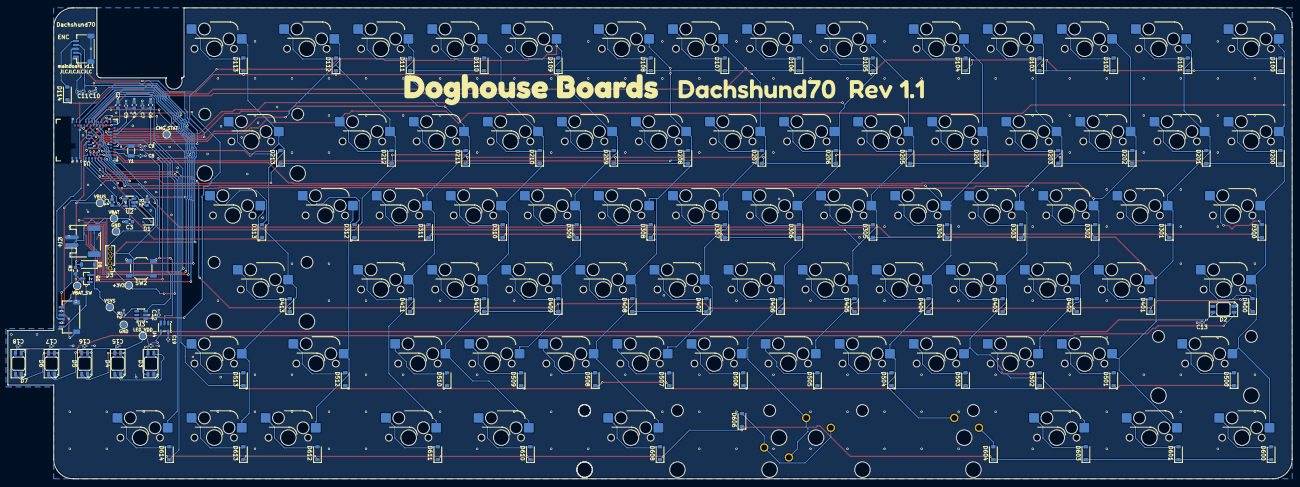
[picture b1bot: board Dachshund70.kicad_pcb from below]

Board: 2 copper layers, 330.3 x 121.1 mm, 217 parts (130 on the bottom side), 134 nets.

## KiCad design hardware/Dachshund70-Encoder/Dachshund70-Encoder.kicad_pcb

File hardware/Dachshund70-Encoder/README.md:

# Dachshund70 encoder module

The roller encoder on its own small board, cabled to the mainboard. Introduced with mainboard Rev 1.1,
which no longer carries the encoder. KiCad 10 project, 2 layers, 1.6 mm FR4.

- **Encoder:** SW1, Bourns PEC12R-2230F-S0024 (shaft parallel to the board, 24 detents, 24 pulses per turn,
  30 mm shaft, push switch pressed along the shaft; no LCSC listing, so source it globally or solder it by hand).
  The 30 mm shaft carries the 2u roller (about 25 mm long, on 19 mm of shaft). Same body and footprint as the
  20 mm PEC12R-2220F-S0024 it replaces (`../3dmodels/Bourns_PEC12R-2x30F-S_standin.step`). Through-hole; its two
  frame tabs are on GND.
- **Cable port:** J1, JST SH 1.0 mm, 5 pins, side entry (SM05B-SRSS-TB), on the **bottom** side, its mouth facing
  +u (toward the shaft). The mainboard's J5 faces it across the notch on the same line, so the cable runs straight
  under the module: about 25 mm overall (housing end to end), 5 parallel wires with both latches on the same side,
  which makes it a reversed cable (J1 pin n to J5 pin 6 − n; the pin numbers below are matched to that). Crimp it
  from SHR-05V-S housings and SSH-003T contacts with 30–32 AWG wire, or shorten a pre-made reversed cable.
  Trim the encoder's through-hole pins to 0.5 mm or less on the bottom: the cable runs right under them (it touches
  the push switch's uncut pins in the model, 0.3 under the A/B/C pins).
- **Nothing else.** The 10 nF debounce capacitors on A and B and the push-switch diode D114 stay on the
  mainboard, so the pin map and the firmware did not change. No expansion ports on either board.

| J5 pin (mainboard) | J1 pin (module) | Net | Encoder pad | MCU pin |
| --- | --- | --- | --- | --- |
| 1 | 5 | COL14 | S1 (push switch) | matrix column 14, with diode D114 on the mainboard |
| 2 | 4 | ENC_A | A | P0.11 |
| 3 | 3 | GND | C (common) | |
| 4 | 2 | ENC_B | B | P0.12 |
| 5 | 1 | ENC_SW | S2 (push switch) | matrix row 0 through D114 |

## Geometry

Module coordinates: u runs along the shaft, toward the hub end of the board (+x of the mainboard's old
encoder); v runs across it (+y); (0, 0) is the board's top-left corner seen from above. Z is measured up
from the PCB's top face.

- Outline 22.5 (u) × 22.0 (v) mm, 1.5 mm corner radius. The right edge is the hub end of the shaft; the wheel
  starts there and the board has nothing under it.
- Encoder pad C at (15.0, 11.0). Body rear face u = 11.5, front face u = 17.5, hub to u = 22.5, shaft tip at
  u = 41.5 (30 mm shaft). Shaft axis at v = 11.0 and 10.0 mm above the PCB top.
- Two mounting holes, 2.2 mm (M2), at (2.7, 2.7) and (2.7, 19.3). The 12.5 mm-wide encoder body spans
  v 4.75 to 17.25.
- J1's pad row at u = 1.3, v = 9 (pin 1) to 13 (pin 5); its body is u 0.8 to 5.8 and its mouth faces +u, so the
  plug sits under the module's left half and the cable leaves toward +u, under the encoder (mainboard x 309.7).
  (Before round 5 it faced -u, into the mainboard's notch edge, where no plug could go in.)
- On the mainboard, J5 is on the back to the right of the corner notch: footprint at (329.8, 49.54) rot 90, pad
  row at x = 331.8 mm, y = 47.54 (pin 5) to 51.54 (pin 1), on the same line as J1 (centre y 49.54, the shaft's
  axis), mouth at x 327.3 facing -x into the notch. The two mouths are 17.6 mm apart; the cable drops 1.8 mm from
  J1 (under the module, z 1.8) to J5 (under the mainboard), and the plate is 7.4 mm above it (6.4 when it floats
  down 1 mm). The notch is open to the mainboard's top edge, x 304.0 to 326.4 mm and y 39.0 to
  57.0 mm, so the module (left edge at x 303.905) sits in it, with a 4.2 mm lobe at (306.6, 57.8) for the
  head of its lower M2 screw (its post is at y 57.82); the upper screw head is inside the notch.

## Status

DRC (kicad-cli, with schematic parity): 0 errors and 0 unconnected items. The only messages are the
library-footprint mismatch on SW1 (the board copy of the footprint is the project's own, like the mainboard's)
and the missing MPN fields that the mainboard also shows. ERC: 0. Not ordered, made or fitted.

LCSC part numbers are blank: the encoder has no LCSC listing (see PROGRESS.md, 2026-10-28), and J1's number
is still to be confirmed, so JLC would source both globally or you solder the encoder by hand.

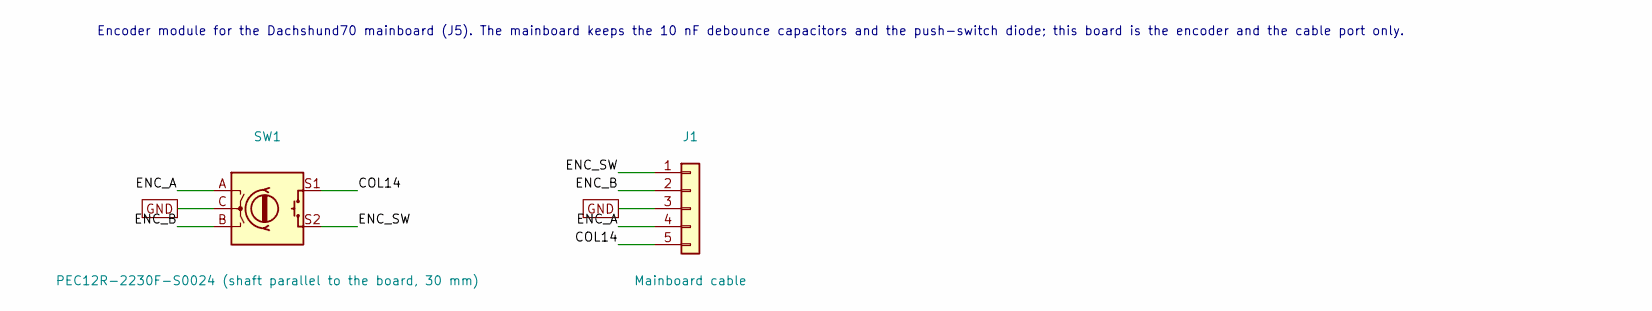
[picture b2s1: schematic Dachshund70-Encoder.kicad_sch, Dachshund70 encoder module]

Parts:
J1: Mainboard cable; JST_SH_SM05B-SRSS-TB_1x05-1MP_P1.00mm_Horizontal; MPN JST SM05B-SRSS-TB
SW1: PEC12R-2230F-S0024 (shaft parallel to the board, 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; RotaryEncoder_Bourns_Horizontal_PEC12R-2x17F-Sxxxx; MPN Bourns PEC12R-2230F-S0024

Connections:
/COL14: J1.5, SW1.S1
/ENC_A: J1.4, SW1.A
/ENC_B: J1.2, SW1.B
/ENC_SW: J1.1, SW1.S2
GND: J1.3, SW1.C

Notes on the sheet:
Encoder module for the Dachshund70 mainboard (J5). The mainboard keeps the 10 nF debounce capacitors and the push-switch diode; this board is the encoder and the cable port only.

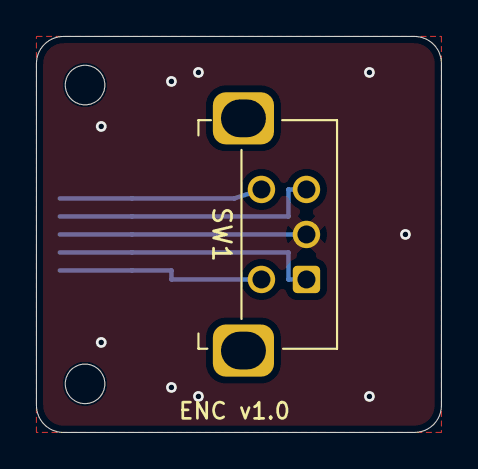
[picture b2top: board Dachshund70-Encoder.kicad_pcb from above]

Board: 2 copper layers, 22.5 x 22.0 mm, 4 parts (1 on the bottom side), 5 nets.

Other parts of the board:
H1, H2: MountingHole_2.2mm_M2
